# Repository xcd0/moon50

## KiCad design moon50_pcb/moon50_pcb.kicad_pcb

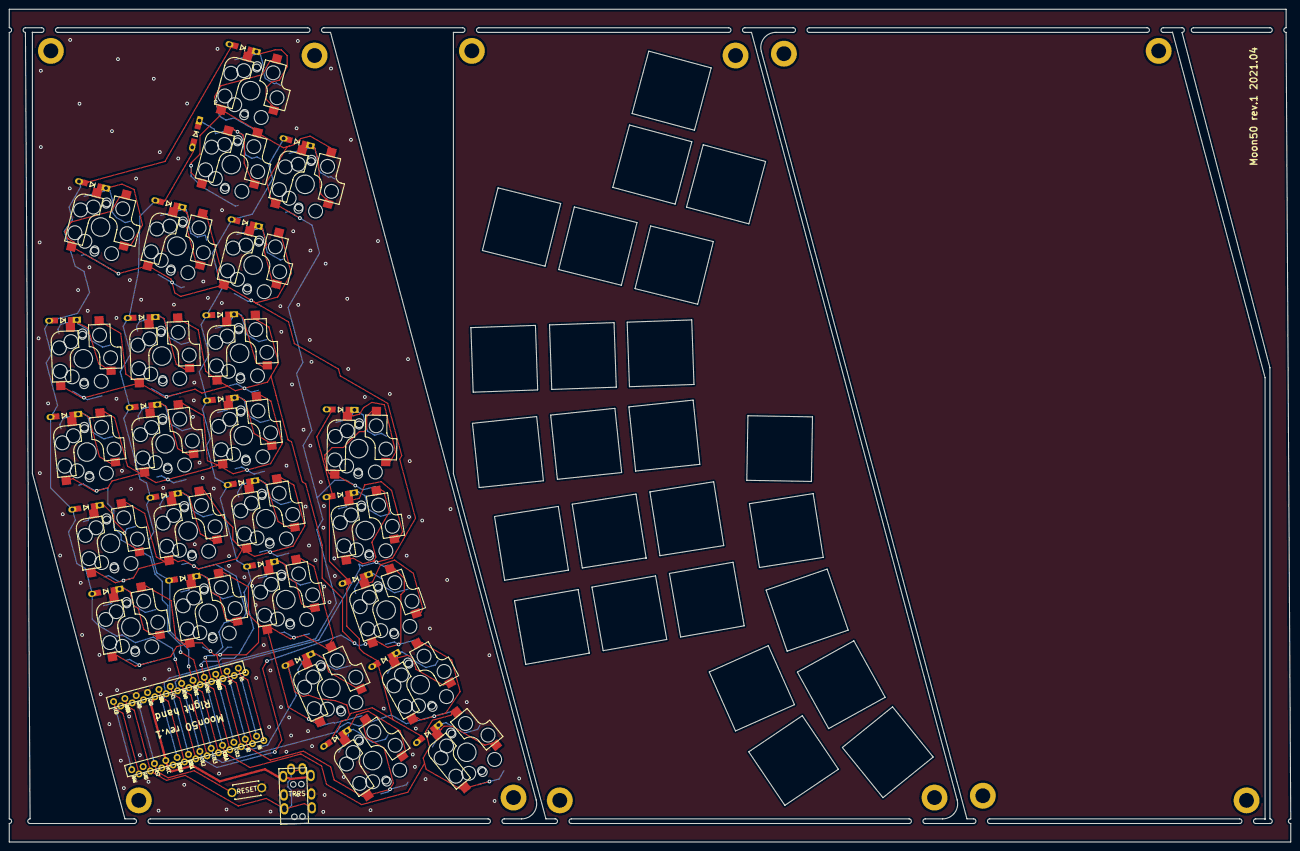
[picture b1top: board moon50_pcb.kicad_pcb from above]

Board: 2 copper layers, 277.0 x 180.0 mm, 53 parts (0 on the bottom side), 40 nets.

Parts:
D1, D2, D3, D4, D5, D6, D7, D8, D9, D10, D11, D12, D13, D14, D15, D16, D17, D18, D19, D20, D21, D22, D23, D24, D25: DIODE; D3_TH_SMD_v2
J1: TRRS; MJ-4PP-9
SW1, SW2, SW3, SW4, SW5, SW6, SW7, SW8, SW9, SW10, SW11, SW12, SW13, SW14, SW15, SW16, SW17, SW18, SW19, SW20, SW21, SW22, SW23, SW24, SW25: KEY; CherryMX_Choc_Hotswap_Narrow
SW26: SW_PUSH; ResetSW_1side
U1: Pro_Micro; ProMicro_v2

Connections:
GND: J1.R1, SW26.1, U1.3, U1.4, U1.23
unnamed: D1.1, SW1.2
unnamed: D2.1, SW2.2
unnamed: D3.1, SW3.2
unnamed: D4.1, SW4.2
unnamed: D5.1, SW5.2
unnamed: D6.1, SW6.2
unnamed: D7.1, SW7.2
unnamed: D8.1, SW8.2
unnamed: D9.1, SW9.2
unnamed: D10.1, SW10.2
unnamed: D11.1, SW11.2
unnamed: D12.1, SW12.2
unnamed: D13.1, SW13.2
unnamed: D14.1, SW14.2
unnamed: D15.1, SW15.2
unnamed: D16.1, SW16.2
unnamed: D17.1, SW17.2
unnamed: D18.1, SW18.2
unnamed: D19.1, SW19.2
unnamed: D20.1, SW20.2
unnamed: D21.1, SW21.2
unnamed: D22.1, SW22.2
unnamed: D23.1, SW23.2
unnamed: D24.1, SW24.2
unnamed: D25.1, SW25.2
col_00: SW19.1, U1.14
col_01: SW1.1, SW7.1, SW13.1, SW20.1, U1.15
col_02: SW2.1, SW8.1, SW14.1, SW21.1, U1.16
col_03: SW3.1, SW9.1, SW15.1, SW22.1, U1.17
col_04: SW4.1, SW10.1, SW16.1, SW23.1, U1.18
col_06: SW5.1, SW11.1, SW17.1, SW24.1, U1.19
col_07: SW6.1, SW12.1, SW18.1, SW25.1, U1.20
data: J1.R2, J1.S, U1.2
row_00: D1.2, D2.2, D3.2, D4.2, D5.2, D6.2, U1.7
row_01: D7.2, D8.2, D9.2, D10.2, D11.2, D12.2, U1.8
row_02: D13.2, D14.2, D15.2, D16.2, D17.2, D18.2, U1.9
row_03: D19.2, D20.2, D21.2, D22.2, D23.2, D24.2, D25.2, U1.10
rst: SW26.2, U1.22
vcc: J1.T, U1.21

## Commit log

2021-06-17 update stl and gcode
